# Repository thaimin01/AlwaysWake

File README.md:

# AlwaysWake
An alarm clock that comes with 4 mechanical switches, a 2.25 inch TFT screen, and runs on rp2040

Features:

- Alarm setting
- Custom music, chirp
- Pomodoro clock
- Countdown clock

This is your average clock, but it's not as annoying as your iphone alarm

Why?

because, you can customize the alarm pattern
Setting up alarm in a quick and easy way
And pomodoro, Countdown for your everyday uses

Schematic

PCB

Case

Bill of materials

| Reference | Qty | Value | DNP | Exclude from BOM | Exclude from Board | Exclude from Simulation | Exclude from Position Files | Footprint | Datasheet |
| :--- | :--- | :--- | :--- | :--- | :--- | :--- | :--- | :--- | :--- |
| BZ1 | 1 | Buzzer | | | | | ${EXCLUDE_FROM_POS_FILES} | Buzzer_Beeper:Buzzer_12x9.5RM7.6 | |
| J1 | 1 | Conn_01x08_Pin | | | | | ${EXCLUDE_FROM_POS_FILES} | Connector_PinSocket_2.54mm:PinSocket_1x08_P2.54mm_Vertical | |
| MX1, MX2, MX4, MX5 | 4 | MX_SW_HS | | | | | ${EXCLUDE_FROM_POS_FILES} | marbastlib-xp-mx:SW_MX_Reversible_1u | |
| U1 | 1 | XIAO-RP2040-SMD | | | | | ${EXCLUDE_FROM_POS_FILES} | Seeed_Studio_XIAO_Series:XIAO-RP2040-SMD | |
| | 4 | M3x8mm Screws | | | | | | | |
| | 4 | M3x16mm Screws | | | | | | | |
| | 8 | M3x5x4 Heatset Inserts | | | | | | | |
| | 8 | 20cm Female-Female Jumper Wires | | | | | | | |

Coding interface

Code by a Human, on Arduino IDE, And C++ !!!

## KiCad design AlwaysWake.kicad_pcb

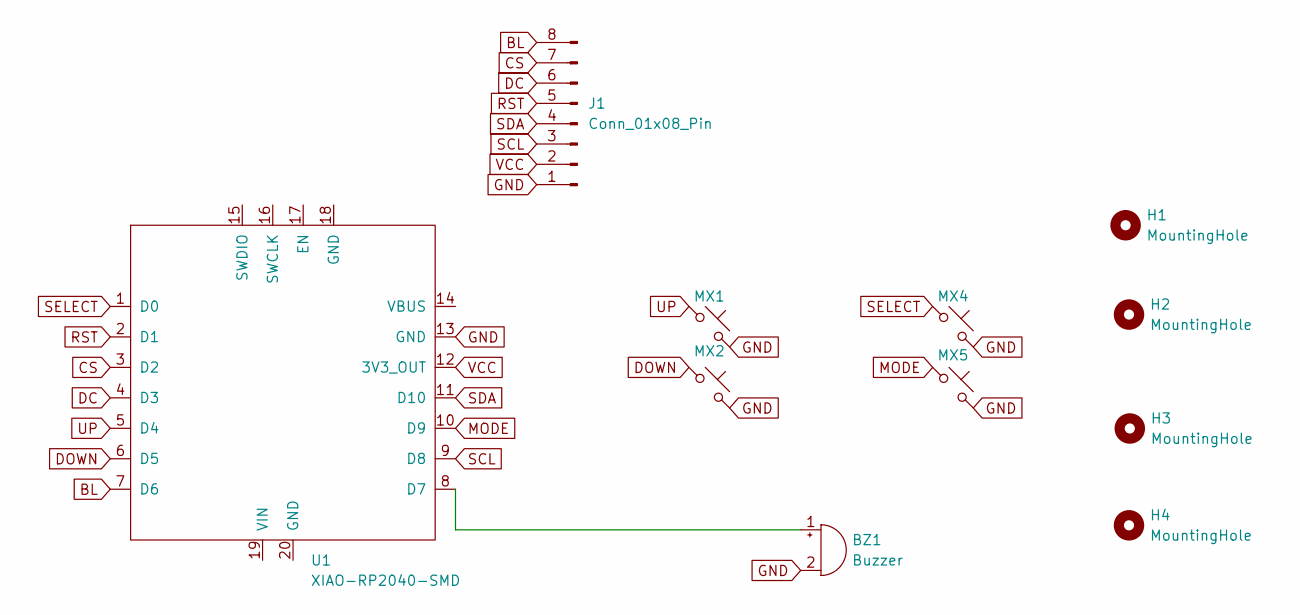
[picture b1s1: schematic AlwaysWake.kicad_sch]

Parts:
BZ1: Buzzer; Buzzer_12x9.5RM7.6
H1, H2, H3, H4: MountingHole; MountingHole_3.2mm_M3
J1: Conn_01x08_Pin; PinSocket_1x08_P2.54mm_Vertical
MX1, MX2, MX4, MX5: MX_SW_HS; SW_MX_Reversible_1u
U1: XIAO-RP2040-SMD

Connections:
BL: J1.8, U1.7 (D6)
CS: J1.7, U1.3 (D2)
DC: J1.6, U1.4 (D3)
DOWN: MX2.1, U1.6 (D5)
GND: BZ1.2 (-), J1.1, MX1.2, MX2.2, MX4.2, MX5.2, U1.13 (GND)
MODE: MX5.1, U1.10 (D9)
unnamed: BZ1.1 (+), U1.8 (D7)
RST: J1.5, U1.2 (D1)
SCL: J1.3, U1.9 (D8)
SDA: J1.4, U1.11 (D10)
SELECT: MX4.1, U1.1 (D0)
UP: MX1.1, U1.5 (D4)
VCC: J1.2, U1.12 (3V3_OUT)

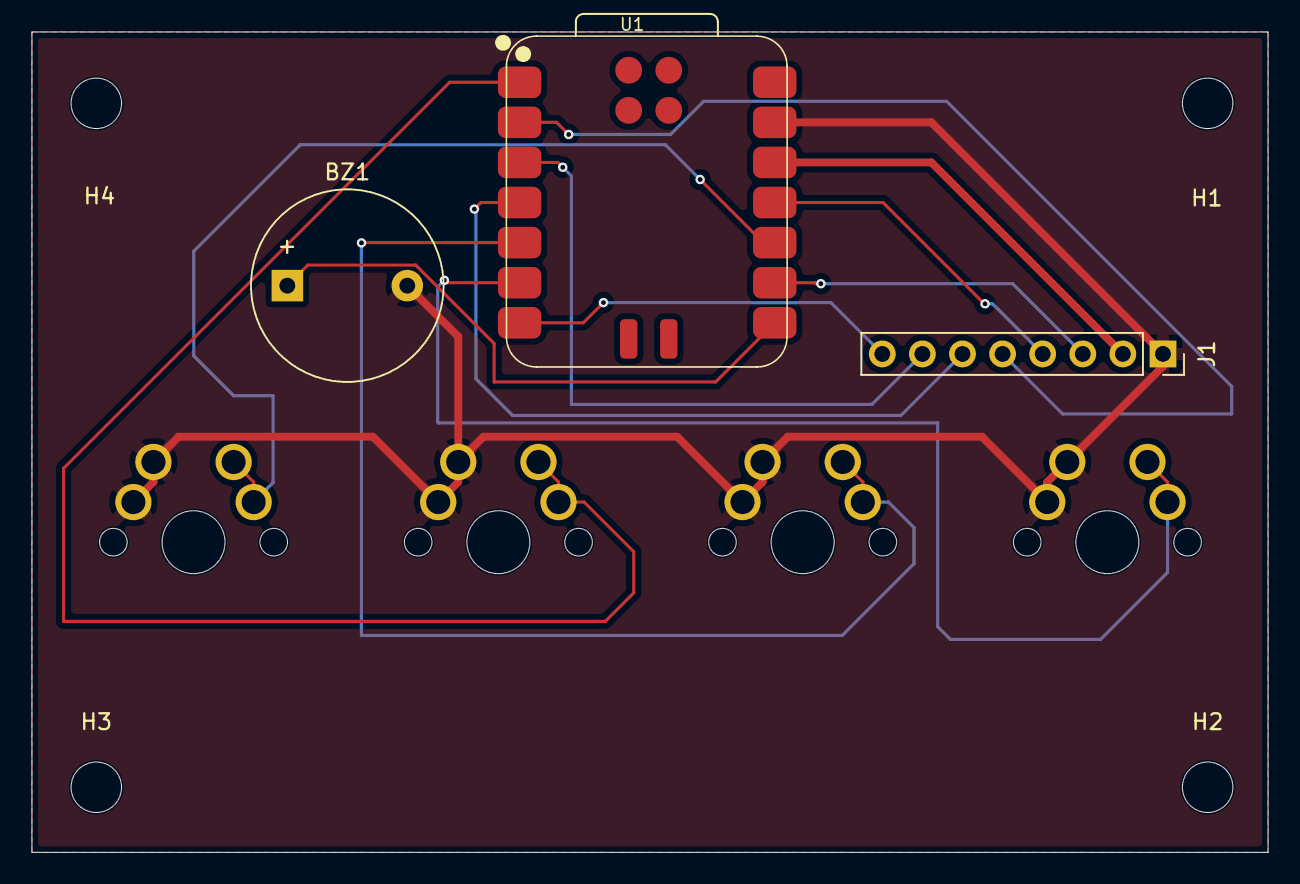
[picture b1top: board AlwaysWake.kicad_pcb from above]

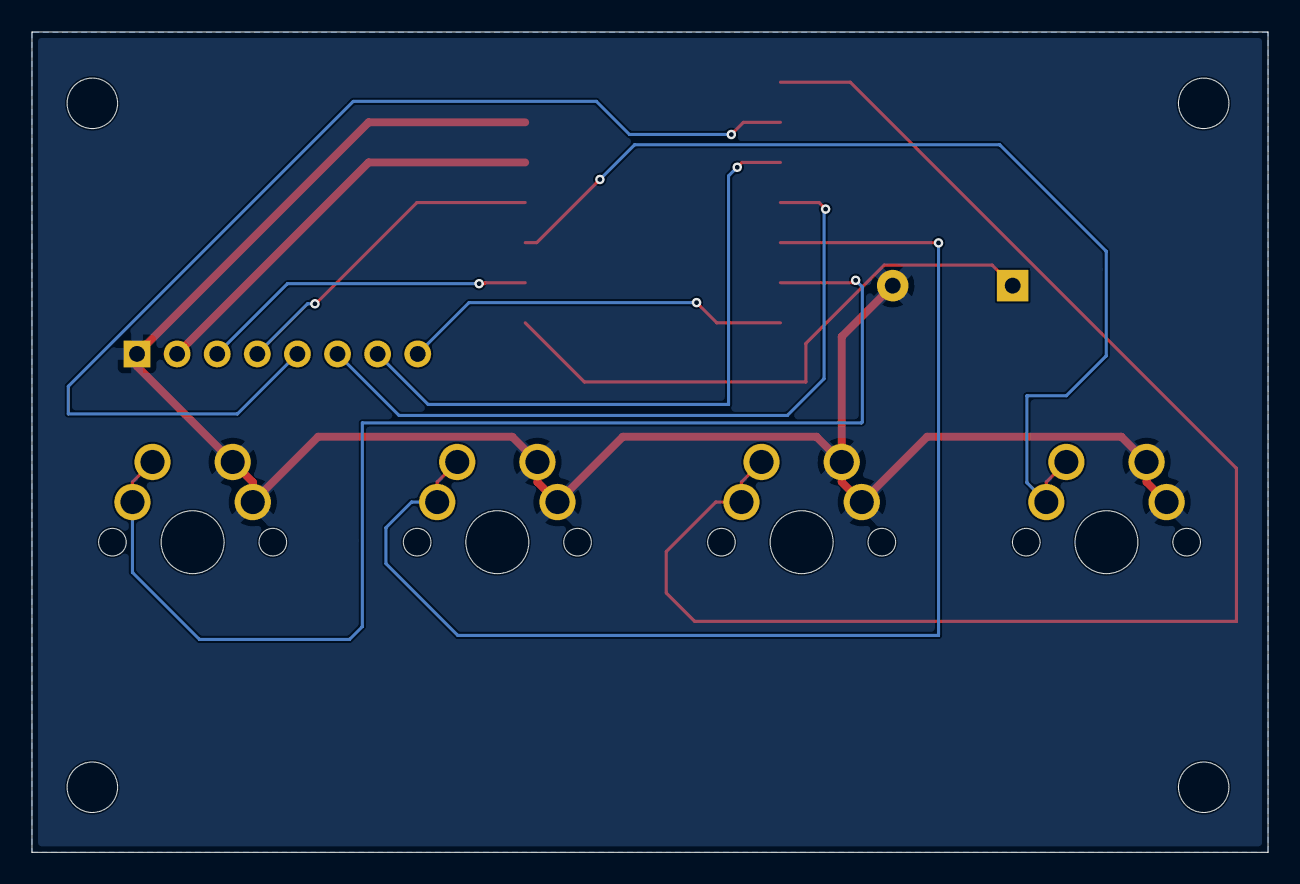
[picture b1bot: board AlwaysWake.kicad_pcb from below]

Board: 2 copper layers, 78.3 x 52.0 mm, 11 parts (4 on the bottom side), 13 nets.
